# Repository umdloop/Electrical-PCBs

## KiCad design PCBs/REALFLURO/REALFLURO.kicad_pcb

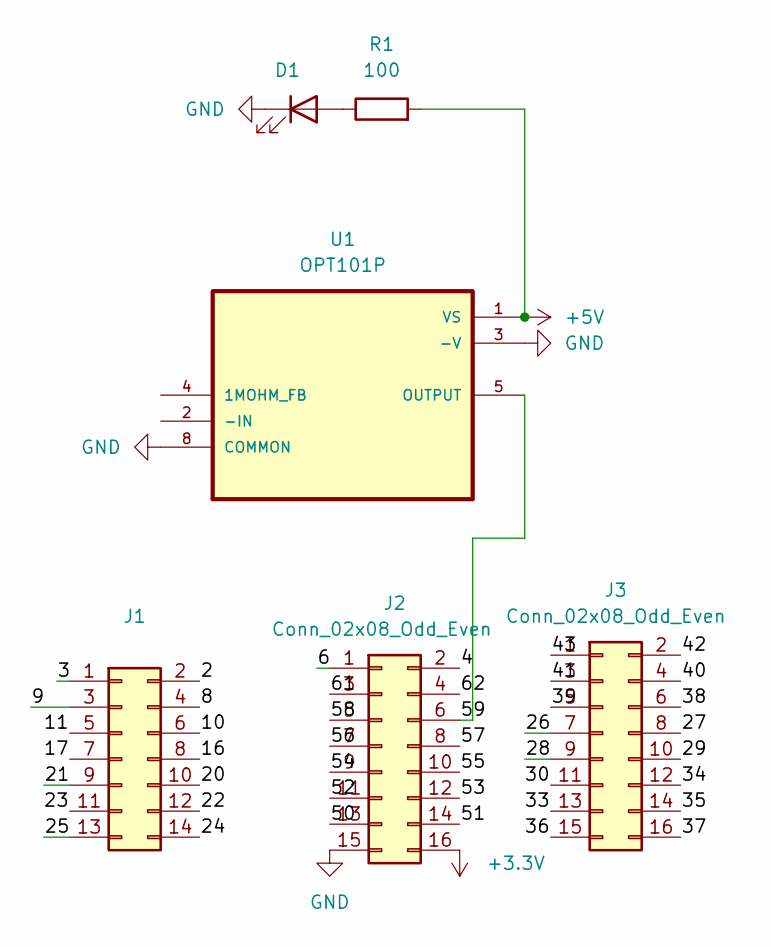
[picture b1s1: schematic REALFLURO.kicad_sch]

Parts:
D1: LED; LED_D3.0mm_Horizontal_O1.27mm_Z2.0mm_Clear
J1: Conn_02x07_Odd_Even; PinHeader_2x07_P2.54mm_Vertical
J2, J3: Conn_02x08_Odd_Even; PinHeader_2x08_P2.54mm_Vertical
R1: 100; R_0201_0603Metric
U1: OPT101P; DIP762W46P254L952H419Q8

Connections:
+3.3V: J2.16
+5V: R1.2, U1.1 (VS)
/2: J1.2
/3: J1.1
/4: J2.2
/6: J2.1
/8: J1.4
/9: J1.3
/10: J1.6
/11: J1.5
/16: J1.8
/17: J1.7
/20: J1.10
/21: J1.9
/22: J1.12
/23: J1.11
/24: J1.14
/25: J1.13
/26: J3.7
/27: J3.8
/28: J3.9
/29: J3.10
/30: J3.11
/33: J3.13
/34: J3.12
/35: J3.14
/36: J3.15
/37: J3.16
/38: J3.6
/39: J3.5
/40: J3.4
/41: J3.3
/42: J3.2
/43: J3.1
/50: J2.13
/51: J2.14
/52: J2.11
/53: J2.12
/54: J2.9
/55: J2.10
/56: J2.7
/57: J2.8
/58: J2.5
/59: J2.6, U1.5 (OUTPUT)
/61: J2.3
/62: J2.4
GND: D1.1 (K), J2.15, U1.3 (-V), U1.8 (COMMON)
unnamed: D1.2 (A), R1.1

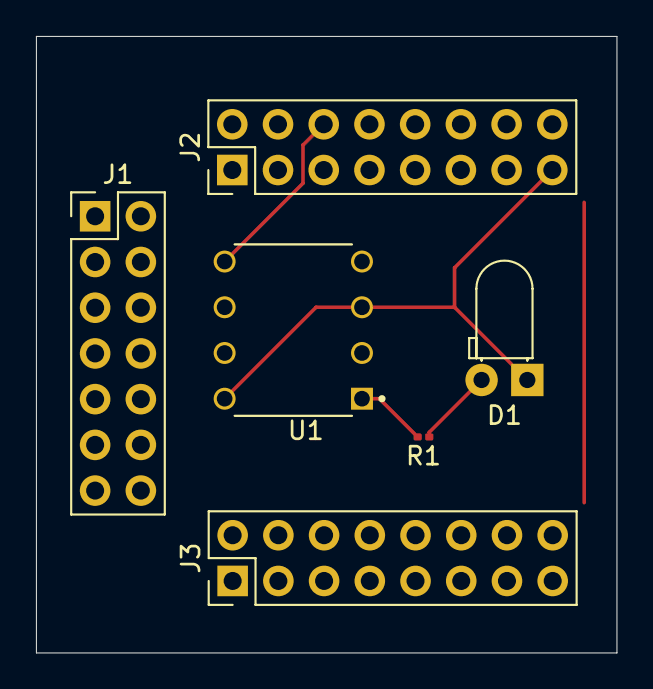
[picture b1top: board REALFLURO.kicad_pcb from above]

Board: 2 copper layers, 32.2 x 34.2 mm, 6 parts (0 on the bottom side), 4 nets.

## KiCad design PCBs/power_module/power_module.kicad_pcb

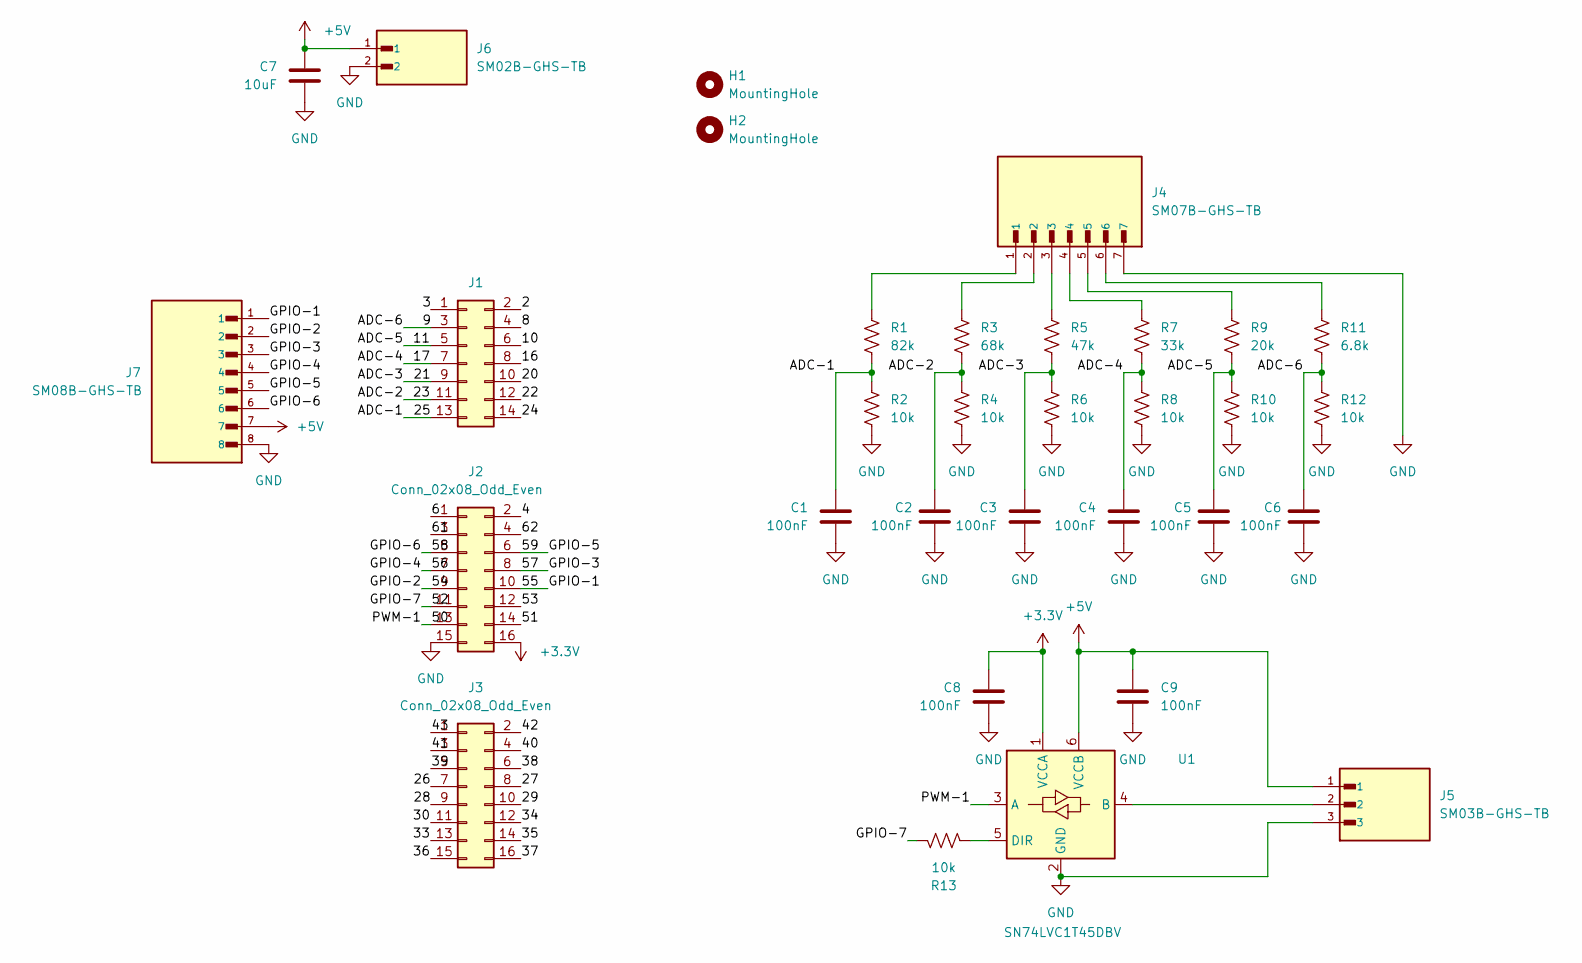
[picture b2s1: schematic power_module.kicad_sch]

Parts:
C1, C2, C3, C4, C5, C6, C8, C9: 100nF; C_0805_2012Metric_Pad1.18x1.45mm_HandSolder
C7: 10uF; C_0805_2012Metric_Pad1.18x1.45mm_HandSolder
H1, H2: MountingHole; MountingHole_3.2mm_M3
J1: Conn_02x07_Odd_Even; PinHeader_2x07_P2.54mm_Vertical
J2, J3: Conn_02x08_Odd_Even; PinHeader_2x08_P2.54mm_Vertical
J4: SM07B-GHS-TB; JST_GH_SM07B-GHS-TB_1x07-1MP_P1.25mm_Horizontal
J5: SM03B-GHS-TB; JST_GH_SM03B-GHS-TB_1x03-1MP_P1.25mm_Horizontal
J6: SM02B-GHS-TB; JST_SM02B-GHS-TB
J7: SM08B-GHS-TB; JST_GH_SM08B-GHS-TB_1x08-1MP_P1.25mm_Horizontal
R1: 82k; R_0805_2012Metric_Pad1.20x1.40mm_HandSolder
R2, R4, R6, R8, R10, R12, R13: 10k; R_0805_2012Metric_Pad1.20x1.40mm_HandSolder
R3: 68k; R_0805_2012Metric_Pad1.20x1.40mm_HandSolder
R5: 47k; R_0805_2012Metric_Pad1.20x1.40mm_HandSolder
R7: 33k; R_0805_2012Metric_Pad1.20x1.40mm_HandSolder
R9: 20k; R_0805_2012Metric_Pad1.20x1.40mm_HandSolder
R11: 6.8k; R_0805_2012Metric_Pad1.20x1.40mm_HandSolder
U1: SN74LVC1T45DBV; SOT-23-6

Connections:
+3.3V: C8.1, J2.16, U1.1 (VCCA)
+5V: C7.1, C9.1, J5.1, J6.1, J7.7, U1.6 (VCCB)
/2: J1.2
/3: J1.1
/4: J2.2
/6: J2.1
/8: J1.4
/9: C6.1, J1.3, R11.2, R12.1
/10: J1.6
/11: C5.1, J1.5, R9.2, R10.1
/16: J1.8
/17: C4.1, J1.7, R7.2, R8.1
/20: J1.10
/21: C3.1, J1.9, R5.2, R6.1
/22: J1.12
/23: C2.1, J1.11, R3.2, R4.1
/24: J1.14
/25: C1.1, J1.13, R1.2, R2.1
/27: J3.8
/29: J3.10
/30: J3.11
/33: J3.13
/34: J3.12
/35: J3.14
/36: J3.15
/37: J3.16
/38: J3.6
/39: J3.5
/40: J3.4
/41: J3.3
/42: J3.2
/43: J3.1
/50: J2.13, U1.3 (A)
/51: J2.14
/52: J2.11, R13.1
/53: J2.12
/54: J2.9, J7.2
/55: J2.10, J7.1
/56: J2.7, J7.4
/57: J2.8, J7.3
/58: J2.5, J7.6
/59: J2.6, J7.5
/61: J2.3
/62: J2.4
GND: C1.2, C2.2, C3.2, C4.2, C5.2, C6.2, C7.2, C8.2, C9.2, J2.15, J4.7, J5.3, J6.2, J7.8, R2.2, R4.2, R6.2, R8.2, R10.2, R12.2, U1.2 (GND)
unnamed: J4.1, R1.1
unnamed: J4.2, R3.1
unnamed: J4.3, R5.1
unnamed: J4.4, R7.1
unnamed: J4.5, R9.1
unnamed: J4.6, R11.1
unnamed: J5.2, U1.4 (B)
unnamed: R13.2, U1.5 (DIR)

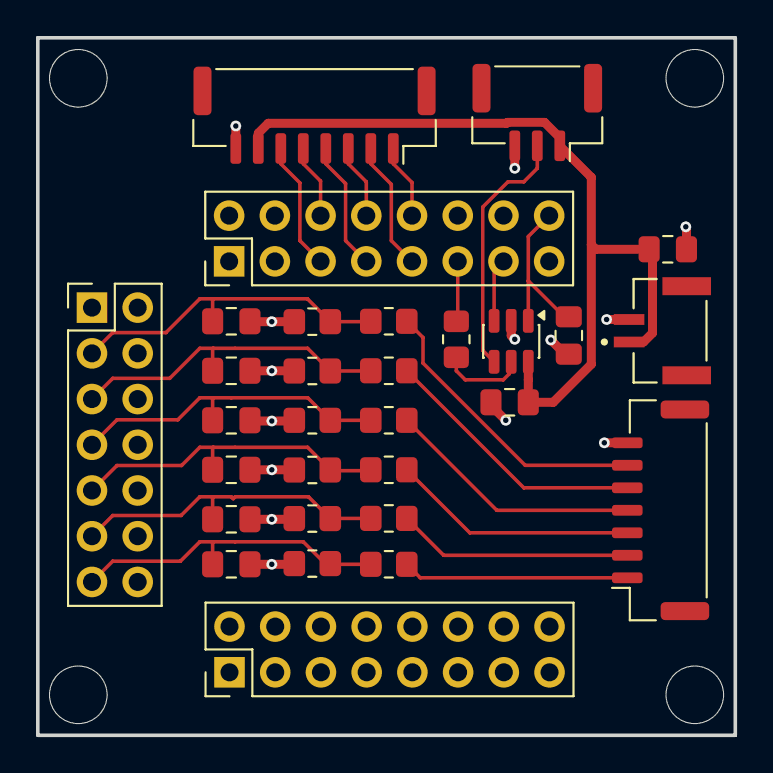
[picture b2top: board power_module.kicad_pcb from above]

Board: 2 copper layers, 38.8 x 38.8 mm, 34 parts (0 on the bottom side), 25 nets.

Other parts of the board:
H3, H4: MountingHole; MountingHole_3.2mm_M3

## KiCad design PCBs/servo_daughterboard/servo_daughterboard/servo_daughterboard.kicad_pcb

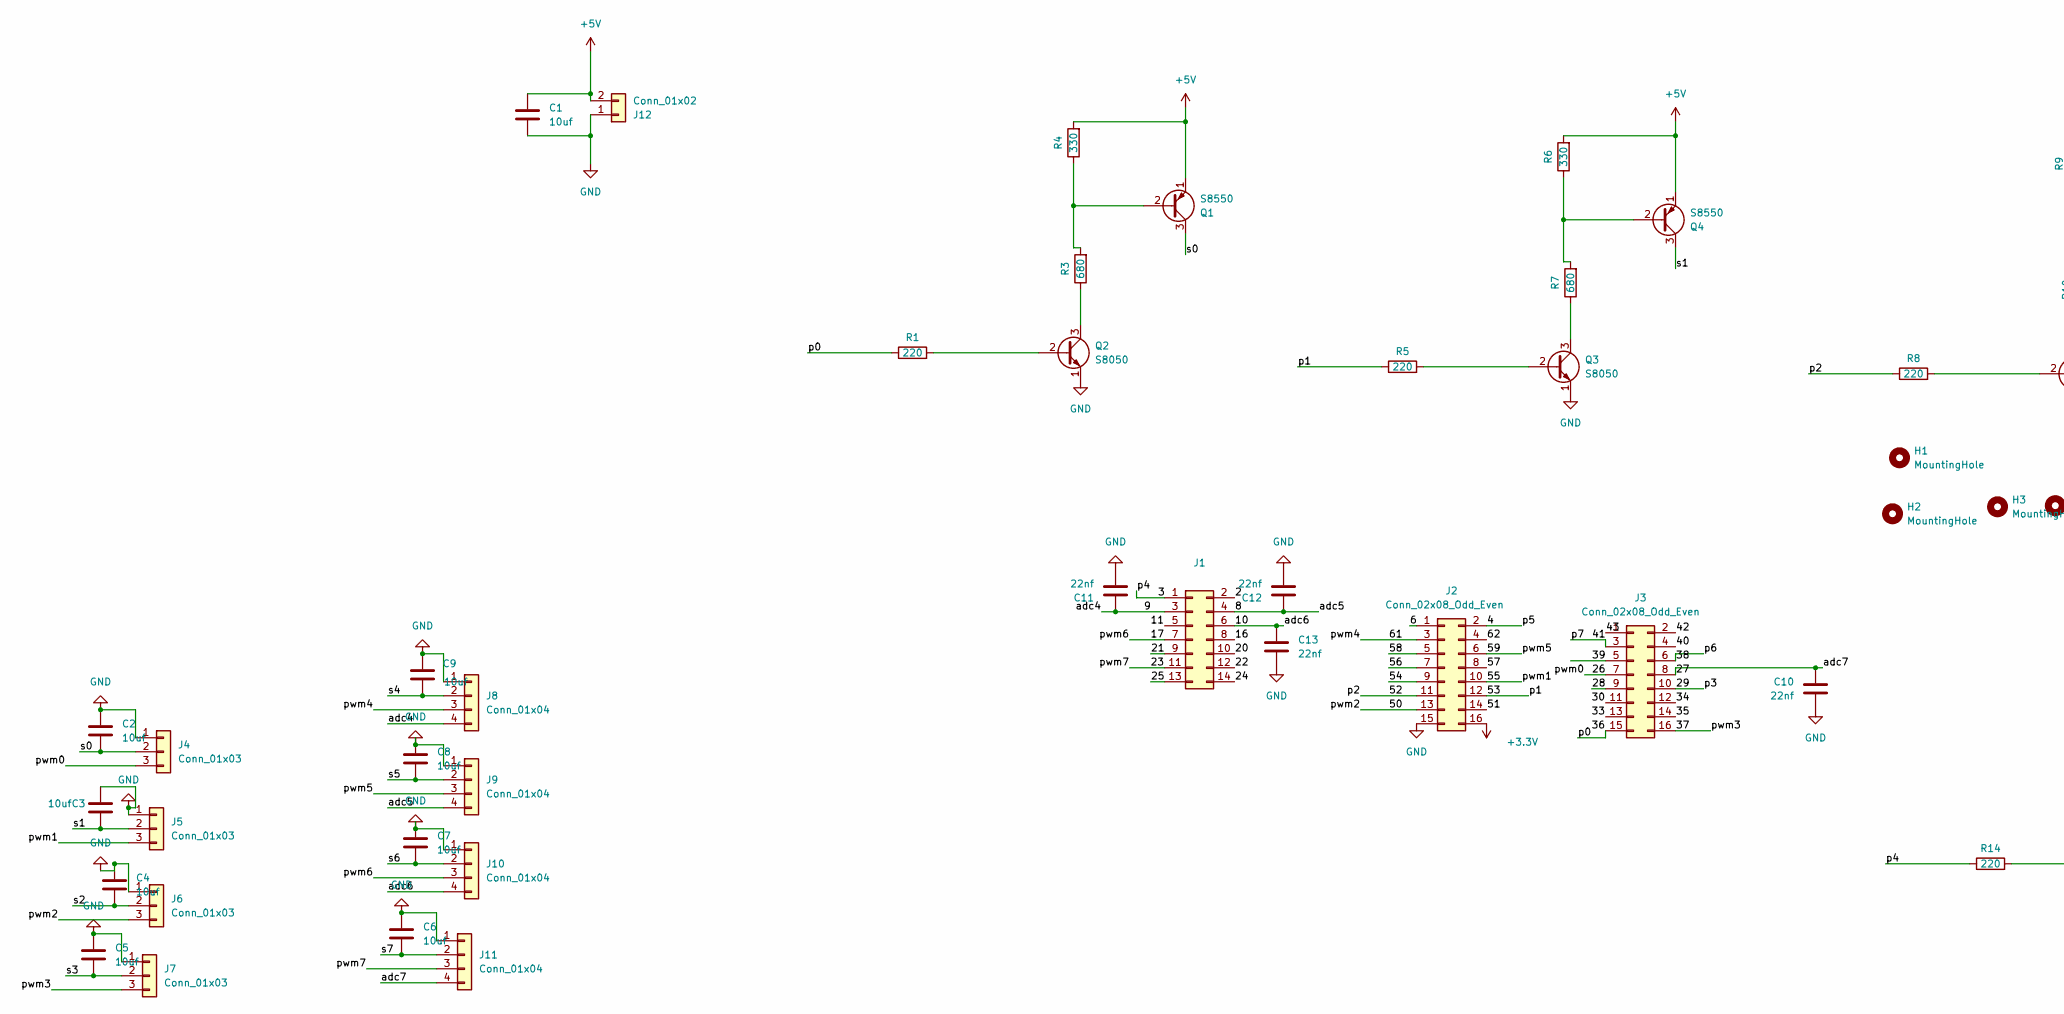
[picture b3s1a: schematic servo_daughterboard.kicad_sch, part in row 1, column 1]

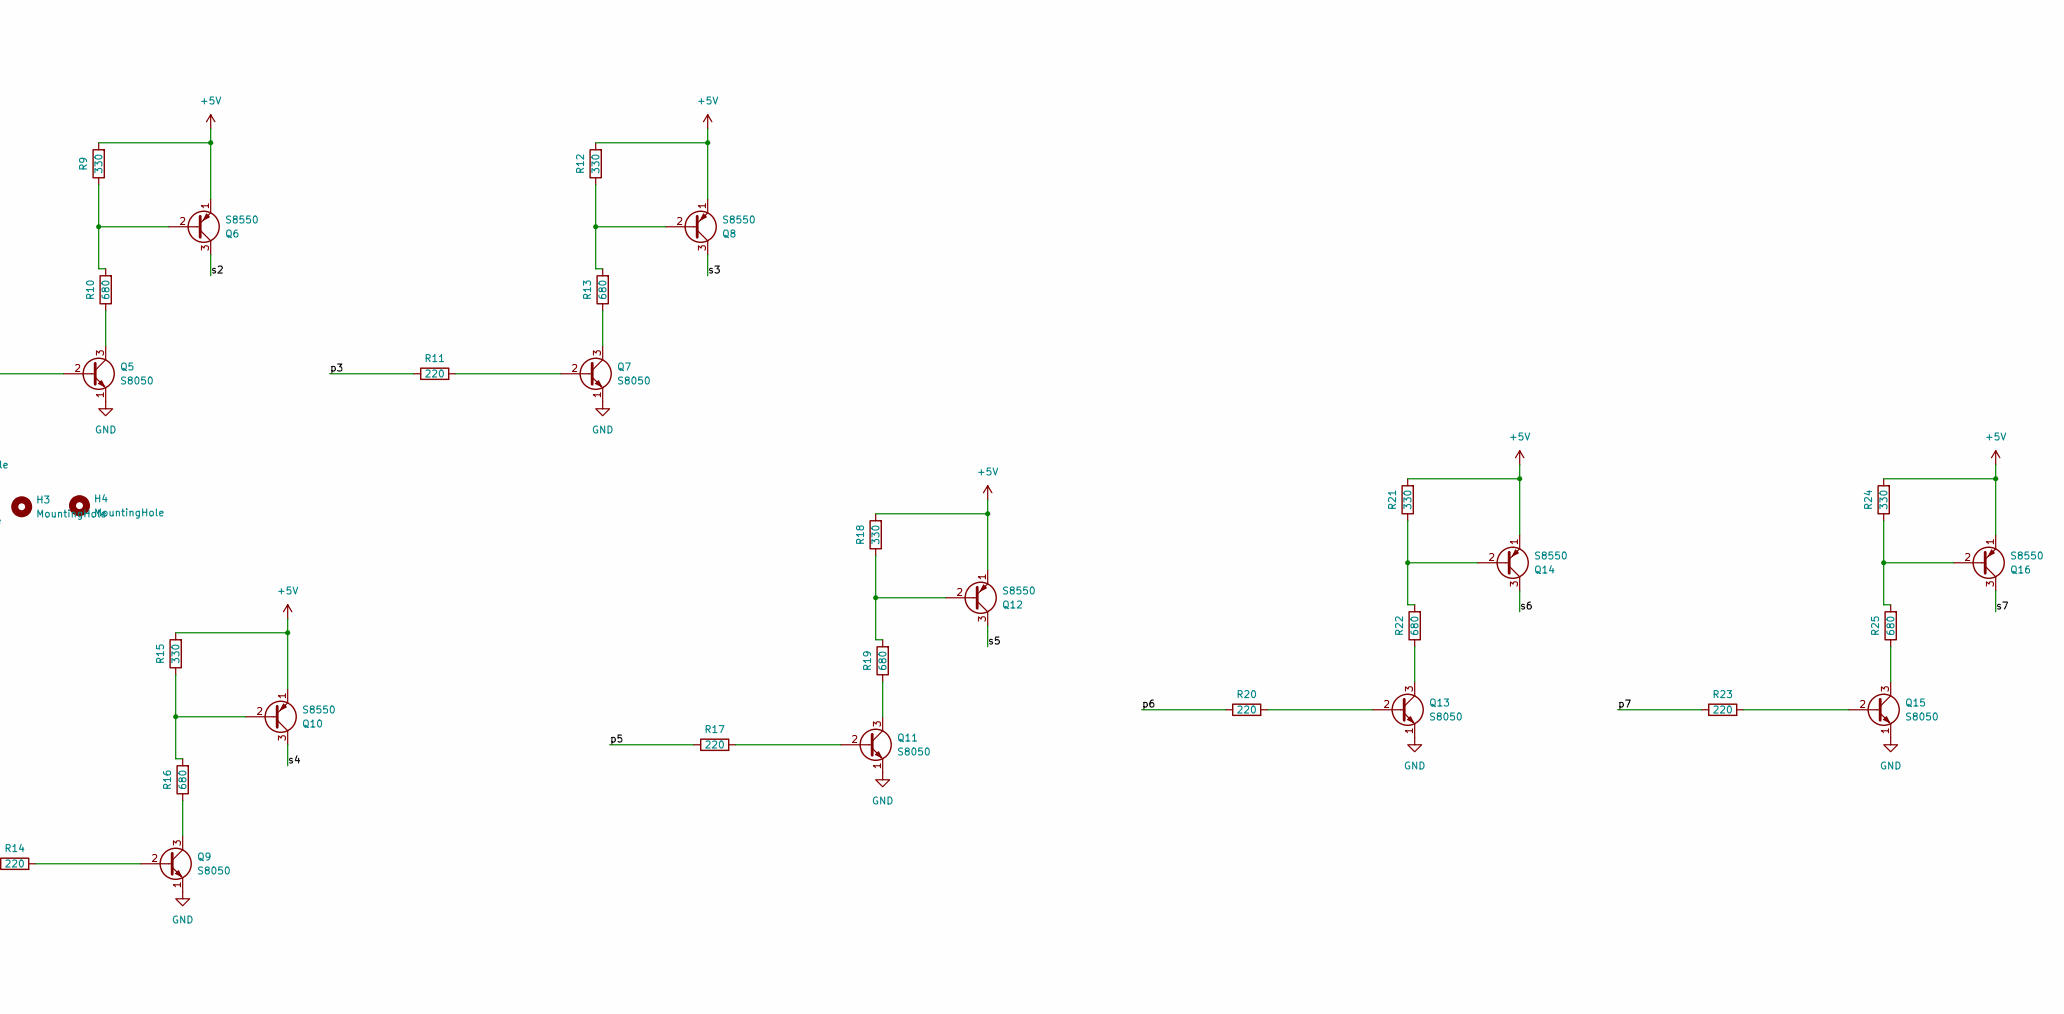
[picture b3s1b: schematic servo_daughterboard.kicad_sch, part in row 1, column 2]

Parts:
C1, C2, C3, C4, C5, C6, C7, C8, C9: 10uf; C_0805_2012Metric_Pad1.18x1.45mm_HandSolder
C10, C11, C12, C13: 22nf; C_0805_2012Metric_Pad1.18x1.45mm_HandSolder
H1, H2, H3, H4: MountingHole; MountingHole_2.2mm_M2
J1: Conn_02x07_Odd_Even; PinHeader_2x07_P2.54mm_Vertical
J2, J3: Conn_02x08_Odd_Even; PinHeader_2x08_P2.54mm_Vertical
J4, J5, J6, J7: Conn_01x03; JST_XH_S3B-XH-A_1x03_P2.50mm_Horizontal
J8, J9, J10, J11: Conn_01x04; JST_XH_S4B-XH-A_1x04_P2.50mm_Horizontal
J12: Conn_01x02; JST_XH_S2B-XH-A_1x02_P2.50mm_Horizontal
Q1, Q4, Q6, Q8, Q10, Q12, Q14, Q16: S8550; TO-92_Inline
Q2, Q3, Q5, Q7, Q9, Q11, Q13, Q15: S8050; TO-92_Inline
R1, R5, R8, R11, R14, R17, R20, R23: 220; R_0402_1005Metric_Pad0.72x0.64mm_HandSolder
R3, R7, R10, R13, R16, R19, R22, R25: 680; R_0402_1005Metric_Pad0.72x0.64mm_HandSolder
R4, R6, R9, R12, R15, R18, R21, R24: 330; R_0402_1005Metric_Pad0.72x0.64mm_HandSolder

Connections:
+3.3V: J2.16
+5V: C1.1, J12.2, Q1.1 (E), Q4.1 (E), Q6.1 (E), Q8.1 (E), Q10.1 (E), Q12.1 (E), Q14.1 (E), Q16.1 (E), R4.2, R6.2, R9.2, R12.2, R15.2, R18.2, R21.2, R24.2
/2: J1.2
/3: J1.1, R14.1
/4: J2.2, R17.1
/6: J2.1
/8: C12.1, J1.4, J9.4
/9: C11.1, J1.3, J8.4
/10: C13.1, J1.6, J10.4
/11: J1.5
/16: J1.8
/17: J1.7, J10.3
/20: J1.10
/21: J1.9
/22: J1.12
/23: J1.11, J11.3
/24: J1.14
/25: J1.13
/26: J3.7, J4.3
/27: C10.1, J3.8, J11.4
/28: J3.9
/29: J3.10, R11.1
/30: J3.11
/33: J3.13
/34: J3.12
/35: J3.14
/36: J3.15, R1.1
/37: J3.16, J7.3
/38: J3.6, R20.1
/39: J3.5
/40: J3.4
/41: J3.3, R23.1
/42: J3.2
/43: J3.1
/50: J2.13, J6.3
/51: J2.14
/52: J2.11, R8.1
/53: J2.12, R5.1
/54: J2.9
/55: J2.10, J5.3
/56: J2.7
/57: J2.8
/58: J2.5
/59: J2.6, J9.3
/61: J2.3, J8.3
/62: J2.4
/s0: C2.2, J4.2, Q1.3 (C)
/s1: C3.2, J5.2, Q4.3 (C)
/s2: C4.2, J6.2, Q6.3 (C)
/s3: C5.2, J7.2, Q8.3 (C)
/s4: C9.2, J8.2, Q10.3 (C)
/s5: C8.2, J9.2, Q12.3 (C)
/s6: C7.2, J10.2, Q14.3 (C)
/s7: C6.2, J11.2, Q16.3 (C)
GND: C1.2, C2.1, C3.1, C4.1, C5.1, C6.1, C7.1, C8.1, C9.1, C10.2, C11.2, C12.2, C13.2, J2.15, J4.1, J5.1, J6.1, J7.1, J8.1, J9.1, J10.1, J11.1, J12.1, Q2.1 (E), Q3.1 (E), Q5.1 (E), Q7.1 (E), Q9.1 (E), Q11.1 (E), Q13.1 (E), Q15.1 (E)
unnamed: Q1.2 (B), R3.2, R4.1
unnamed: Q2.2 (B), R1.2
unnamed: Q2.3 (C), R3.1
unnamed: Q3.2 (B), R5.2
unnamed: Q3.3 (C), R7.1
unnamed: Q4.2 (B), R6.1, R7.2
unnamed: Q5.2 (B), R8.2
unnamed: Q5.3 (C), R10.1
unnamed: Q6.2 (B), R9.1, R10.2
unnamed: Q7.2 (B), R11.2
unnamed: Q7.3 (C), R13.1
unnamed: Q8.2 (B), R12.1, R13.2
unnamed: Q9.2 (B), R14.2
unnamed: Q9.3 (C), R16.1
unnamed: Q10.2 (B), R15.1, R16.2
unnamed: Q11.2 (B), R17.2
unnamed: Q11.3 (C), R19.1
unnamed: Q12.2 (B), R18.1, R19.2
unnamed: Q13.2 (B), R20.2
unnamed: Q13.3 (C), R22.1
unnamed: Q14.2 (B), R21.1, R22.2
unnamed: Q15.2 (B), R23.2
unnamed: Q15.3 (C), R25.1
unnamed: Q16.2 (B), R24.1, R25.2

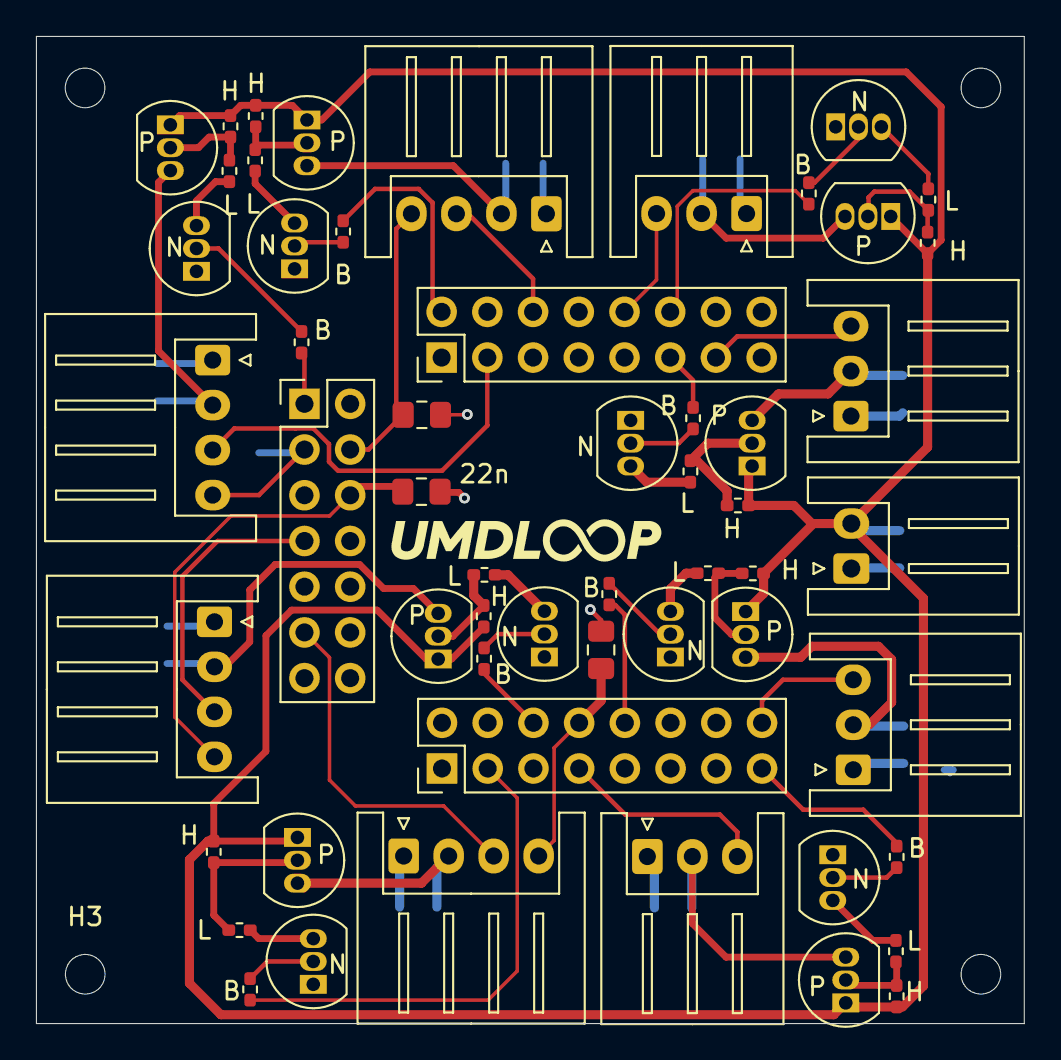
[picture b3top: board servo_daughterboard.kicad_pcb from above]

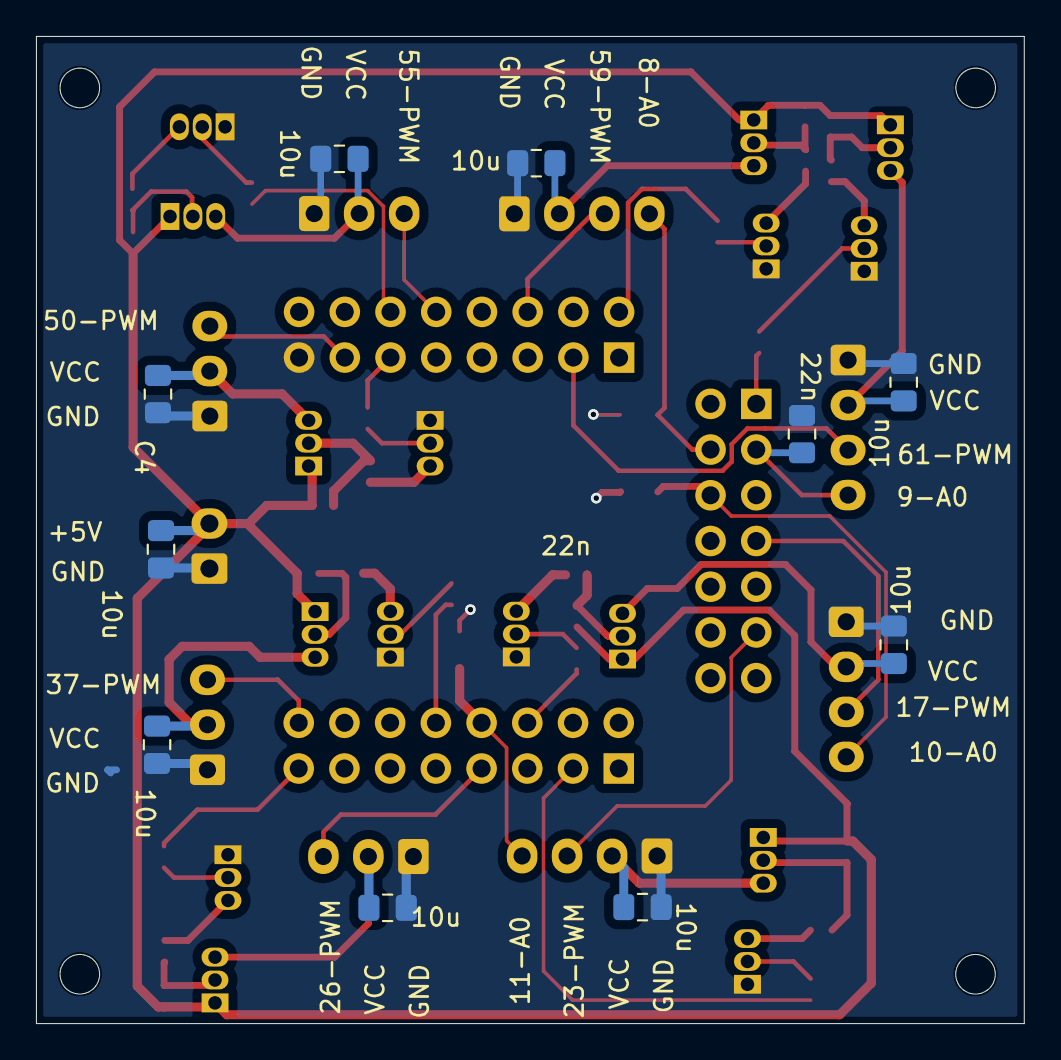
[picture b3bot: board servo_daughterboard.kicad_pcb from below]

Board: 2 copper layers, 54.9 x 54.8 mm, 69 parts (10 on the bottom side), 54 nets.

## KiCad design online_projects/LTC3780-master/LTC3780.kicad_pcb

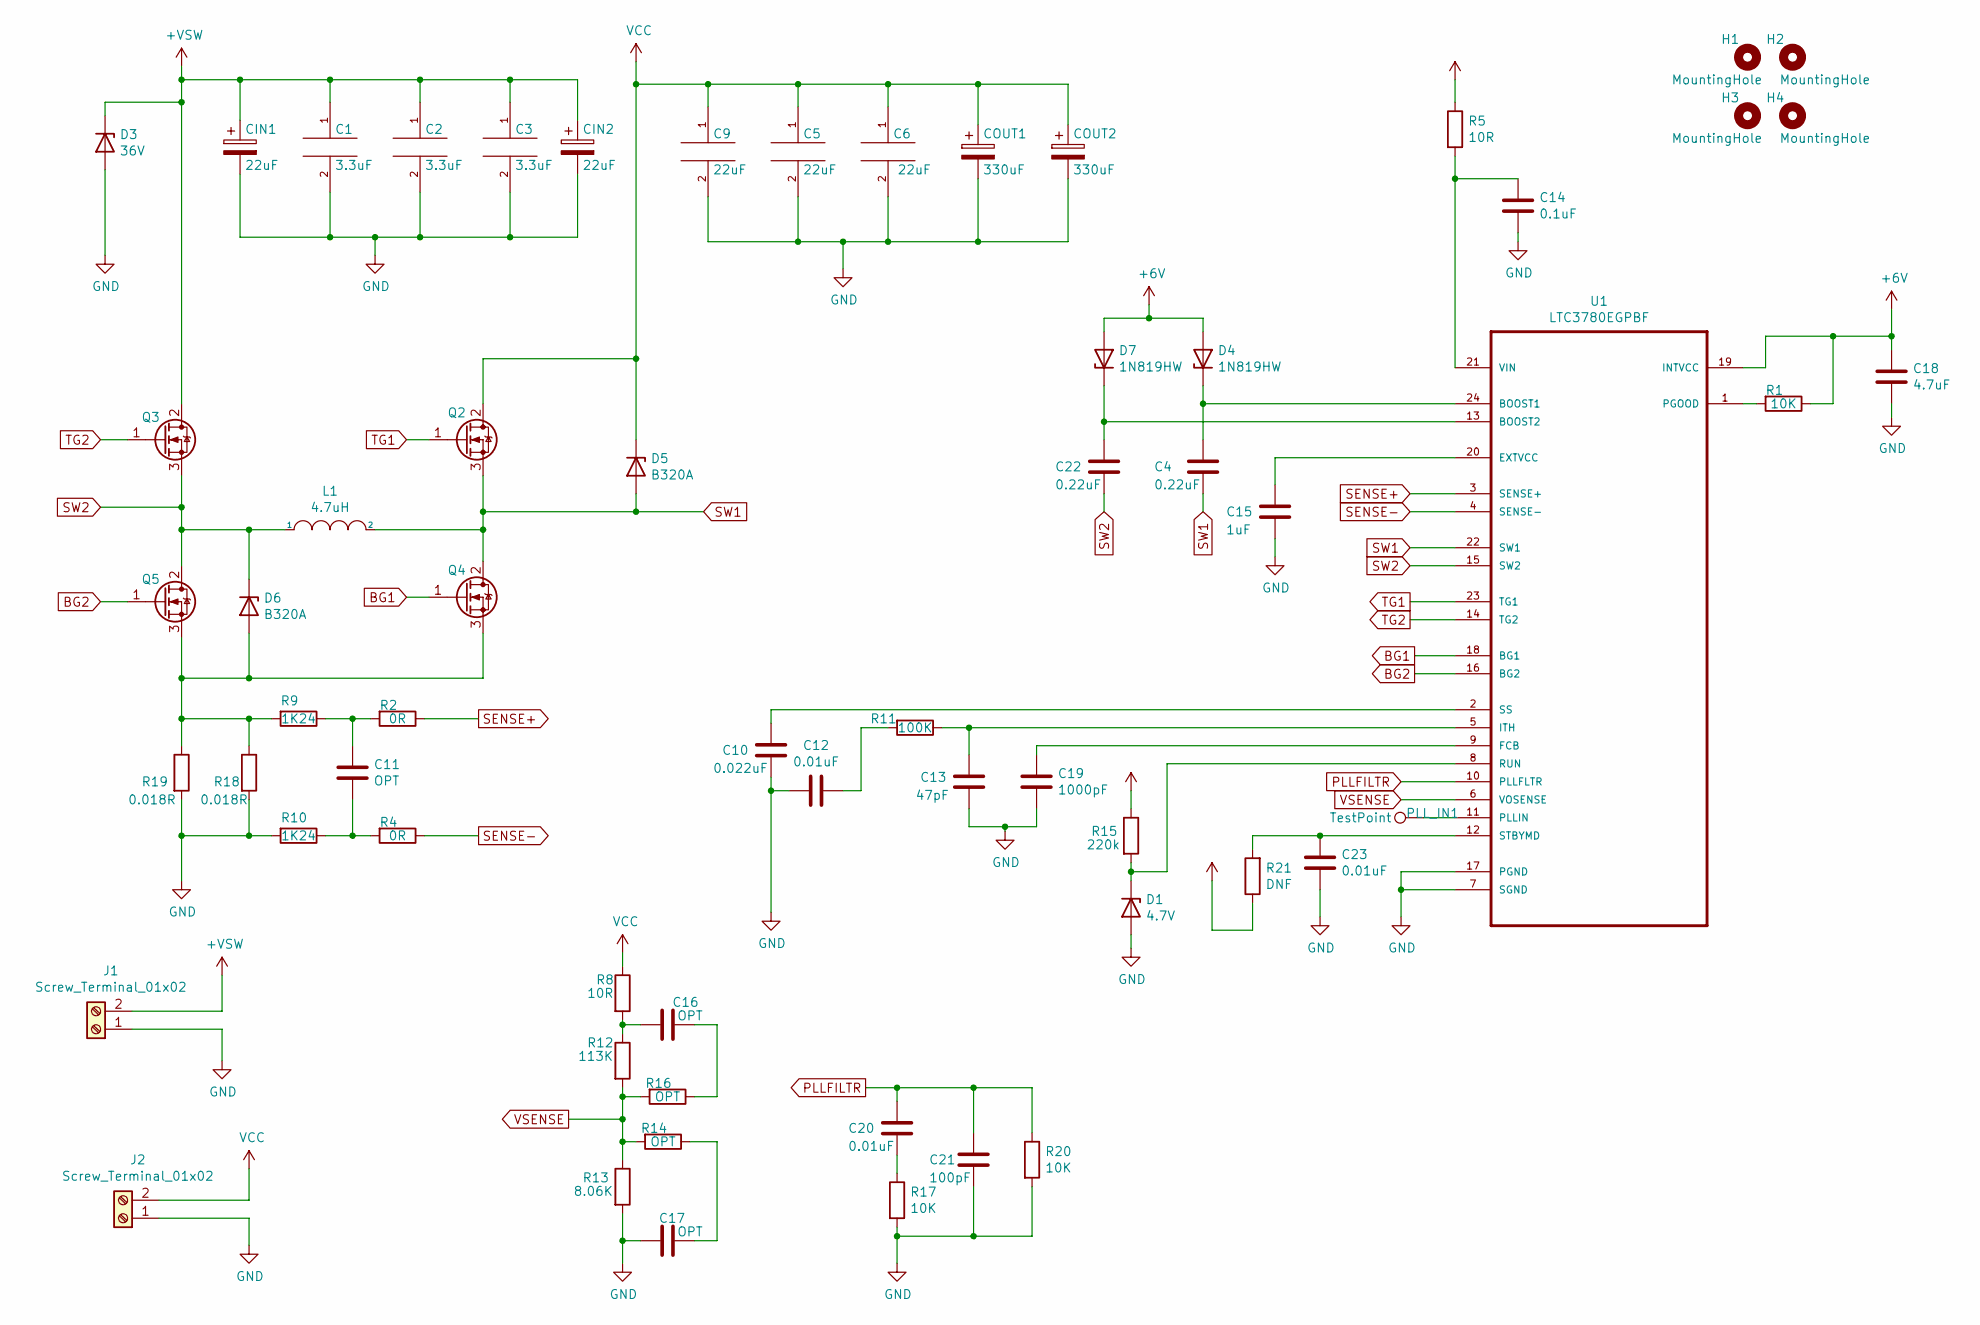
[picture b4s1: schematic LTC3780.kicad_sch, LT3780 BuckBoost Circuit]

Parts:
C1, C2, C3: 3.3uF; C_0603_HandSoldering
C4, C22: 0.22uF; C_0603_HandSoldering
C5, C6, C9: 22uF; C_0603_HandSoldering
C10: 0.022uF; C_0603_HandSoldering
C11, C16, C17: OPT; C_0603_HandSoldering
C12, C20, C23: 0.01uF; C_0603_HandSoldering
C13: 47pF; C_0603_HandSoldering
C14: 0.1uF; C_0603_HandSoldering
C15: 1uF; C_0603_HandSoldering
C18: 4.7uF; C_0603_HandSoldering
C19: 1000pF; C_0603_HandSoldering
C21: 100pF; C_0603_HandSoldering
CIN1, CIN2: 22uF; CP_Elec_8x6.7
COUT1, COUT2: 330uF; CP_Elec_8x10.5
D1: 4.7V; D_SOD-323_HandSoldering
D3: 36V; D_SOT-23_ANK
D4, D7: 1N819HW; D_SOD-123
D5, D6: B320A; D_SMA_Handsoldering
H1, H2, H3, H4: MountingHole; MountingHole_4mm
J1, J2: Screw_Terminal_01x02; JST_VH_B2P-VH_2x3.96mm_Vertical
L1: 4.7uH; Inductor_Wurth_MAPI-4020
PLL_IN1: TestPoint; Measurement_Point_Square-SMD-Pad_Small
Q2, Q3, Q4, Q5: IPD100N04S402ATMA1; TO-252-2
R1, R17, R20: 10K; R_0603_HandSoldering
R2, R4: 0R; R_0603_HandSoldering
R5, R8: 10R; R_0603_HandSoldering
R9, R10: 1K24; R_0603_HandSoldering
R11: 100K; R_0603_HandSoldering
R12: 113K; R_0603_HandSoldering
R13: 8.06K; R_0603_HandSoldering
R14, R16: OPT; R_0603_HandSoldering
R15: 220k; R_0603_HandSoldering
R18, R19: 0.018R; R_2512_HandSoldering
R21: DNF; R_0603_HandSoldering
U1: LTC3780EGPBF; SOP65P780X200-24N

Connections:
+6V: C18.1, D4.2 (A), D7.2 (A), R1.1, U1.19 (INTVCC)
+VSW: C1.1, C2.1, C3.1, CIN1.1, CIN2.1, D3.1 (K), J1.2, Q3.2, R5.1, R15.1, R21.1
BG1: Q4.1, U1.18 (BG1)
BG2: Q5.1, U1.16 (BG2)
GND: C1.2, C2.2, C3.2, C5.2, C6.2, C9.2, C10.2, C12.2, C13.2, C14.2, C15.1, C17.2, C18.2, C19.2, C21.2, C23.2, CIN1.2, CIN2.2, COUT1.2, COUT2.2, D1.2 (A), D3.2 (A), J1.1, J2.1, R10.2, R13.2, R17.2, R18.2, R19.2, R20.2, U1.7 (SGND), U1.17 (PGND)
unnamed: C4.1, D4.1 (K), U1.24 (BOOST1)
unnamed: C10.1, U1.2 (SS)
unnamed: C11.1, R2.2, R9.1
unnamed: C11.2, R4.2, R10.1
unnamed: C12.1, R11.2
unnamed: C13.1, R11.1, U1.5 (ITH)
unnamed: C14.1, R5.2, U1.21 (VIN)
unnamed: C15.2, U1.20 (EXTVCC)
unnamed: C16.1, R16.1
unnamed: C16.2, R8.2, R12.1
unnamed: C17.1, R14.1
unnamed: C19.1, U1.9 (FCB)
unnamed: C20.2, R17.1
unnamed: C22.1, D7.1 (K), U1.13 (BOOST2)
unnamed: C23.1, R21.2, U1.12 (STBYMD)
unnamed: D1.1 (K), R15.2, U1.8 (RUN)
unnamed: D6.2 (A), Q4.3, Q5.3, R9.2, R18.1, R19.1
unnamed: PLL_IN1.1, U1.11 (PLLIN)
unnamed: R1.2, U1.1 (PGOOD)
PLLFILTR: C20.1, C21.1, R20.1, U1.10 (PLLFLTR)
SENSE+: R2.1, U1.3 (SENSE+)
SENSE-: R4.1, U1.4 (SENSE-)
SW1: C4.2, D5.2 (A), L1.2, Q2.3, Q4.2, U1.22 (SW1)
SW2: C22.2, D6.1 (K), L1.1, Q3.3, Q5.2, U1.15 (SW2)
TG1: Q2.1, U1.23 (TG1)
TG2: Q3.1, U1.14 (TG2)
VCC: C5.1, C6.1, C9.1, COUT1.1, COUT2.1, D5.1 (K), J2.2, Q2.2, R8.1
VSENSE: R12.2, R13.1, R14.2, R16.2, U1.6 (VOSENSE)

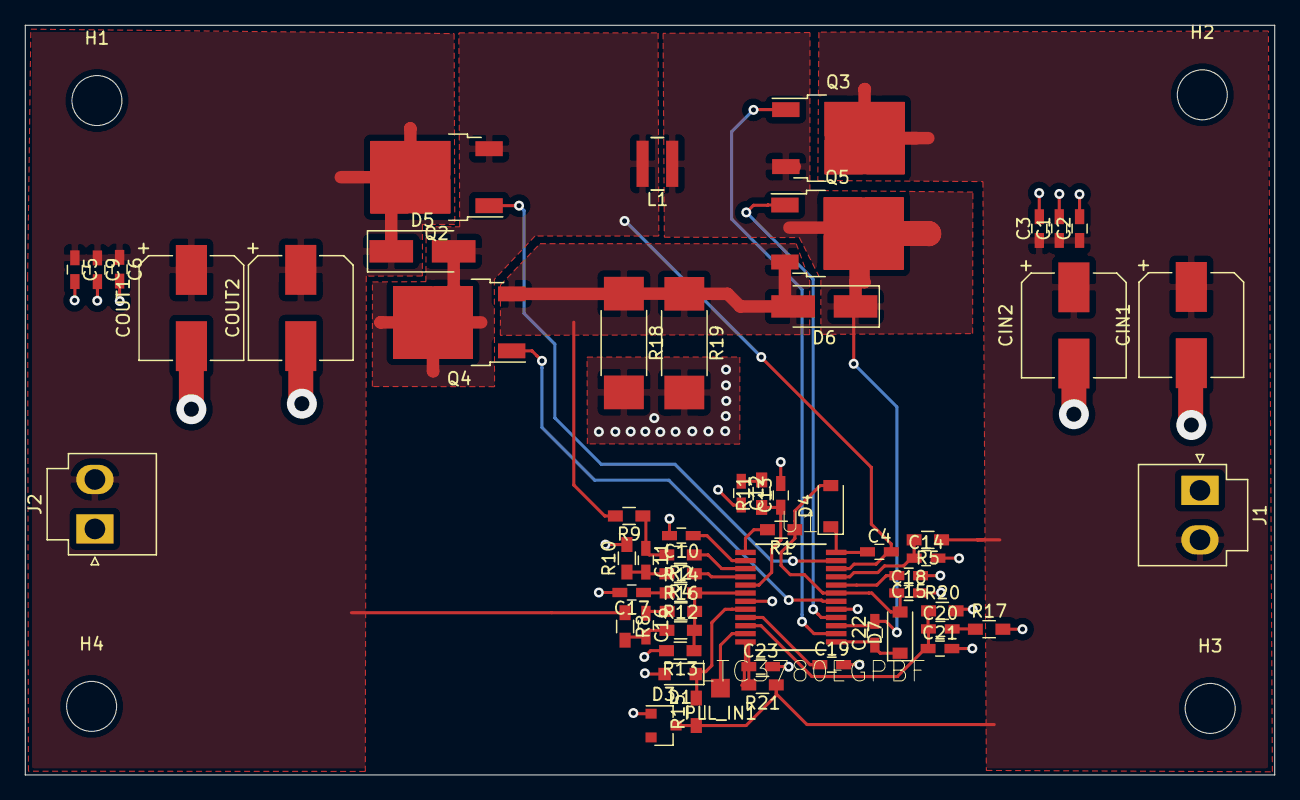
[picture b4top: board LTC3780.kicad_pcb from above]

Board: 2 copper layers, 100.0 x 60.0 mm, 62 parts (0 on the bottom side), 33 nets.

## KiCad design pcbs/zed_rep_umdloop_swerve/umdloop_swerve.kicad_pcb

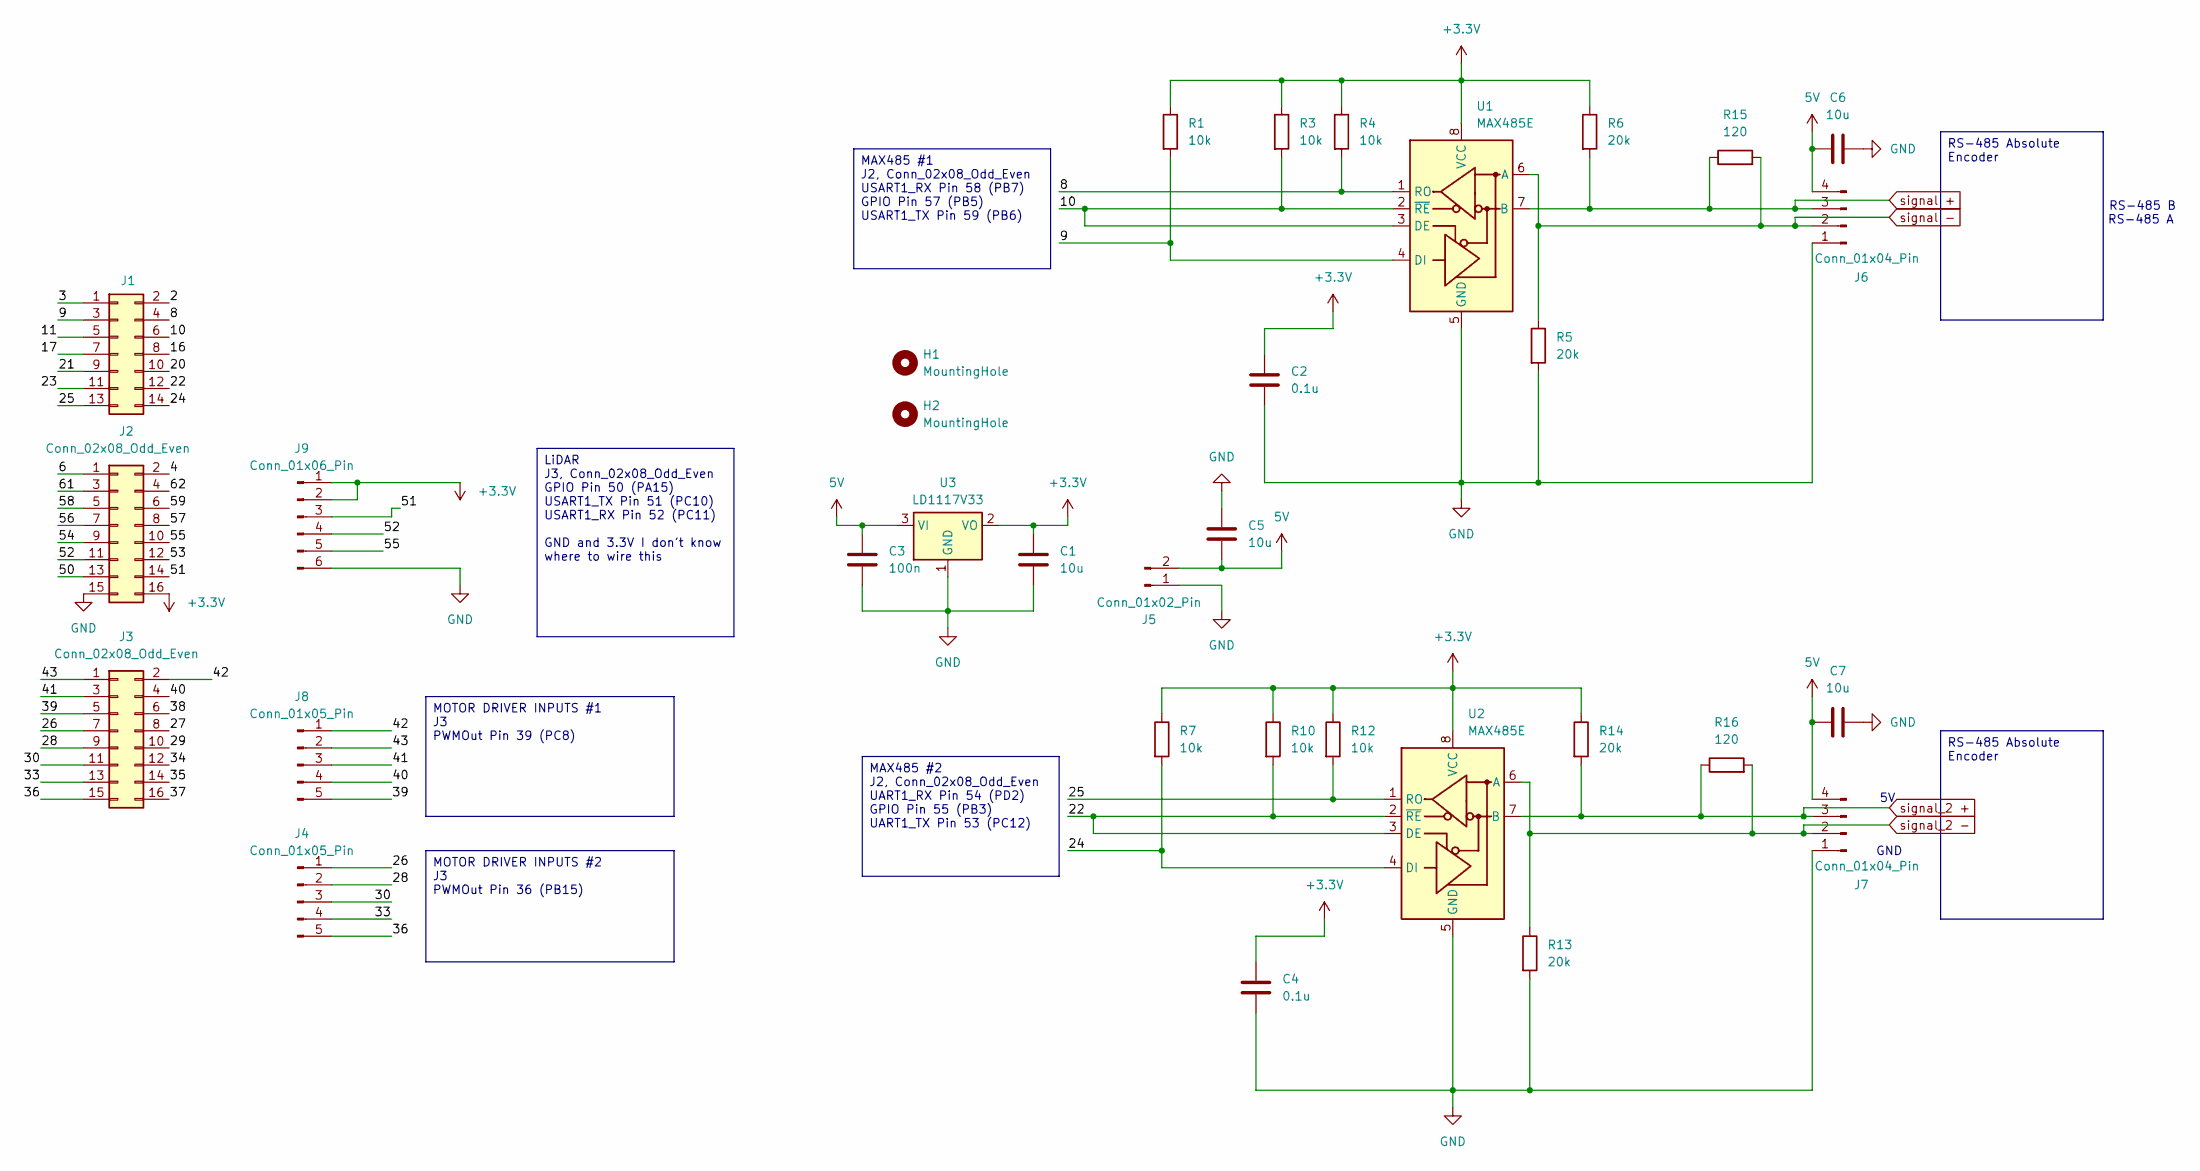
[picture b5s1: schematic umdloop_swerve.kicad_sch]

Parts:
C1, C5, C6, C7: 10u; C_0805_2012Metric_Pad1.18x1.45mm_HandSolder
C2, C4: 0.1u; C_0402_1005Metric_Pad0.74x0.62mm_HandSolder
C3: 100n; C_0805_2012Metric_Pad1.18x1.45mm_HandSolder
H1, H2: MountingHole; MountingHole_3.2mm_M3
J1: Conn_02x07_Odd_Even; PinHeader_2x07_P2.54mm_Vertical
J2, J3: Conn_02x08_Odd_Even; PinHeader_2x08_P2.54mm_Vertical
J4, J8: Conn_01x05_Pin; JST_XH_S5B-XH-A_1x05_P2.50mm_Horizontal
J5: Conn_01x02_Pin; JST_XH_S2B-XH-A_1x02_P2.50mm_Horizontal
J6, J7: Conn_01x04_Pin; JST_XH_S4B-XH-A_1x04_P2.50mm_Horizontal
J9: Conn_01x06_Pin; JST_XH_S6B-XH-A_1x06_P2.50mm_Horizontal
R1, R3, R4, R7, R10, R12: 10k; R_0402_1005Metric_Pad0.72x0.64mm_HandSolder
R5, R6, R13, R14: 20k; R_0402_1005Metric_Pad0.72x0.64mm_HandSolder
R15, R16: 120; R_0402_1005Metric_Pad0.72x0.64mm_HandSolder
U1, U2: MAX485E; SOIC-8_3.9x4.9mm_P1.27mm
U3: LD1117V33; SOT-223-3_TabPin2

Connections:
5V: C3.1, C5.1, C6.1, C7.1, J5.2, J6.4, J7.4, U3.3 (VI)
+3.3V: C1.1, C2.1, C4.1, J2.16, J9.1, J9.2, R1.1, R3.1, R4.1, R6.1, R7.1, R10.1, R12.1, R14.1, U1.8 (VCC), U2.8 (VCC), U3.2 (VO)
/2: J1.2
/3: J1.1
/4: J2.2
/6: J2.1
/8: J1.4, R4.2, U1.1 (RO)
/9: J1.3, R1.2, U1.4 (DI)
/10: J1.6, R3.2, U1.2 (~RE), U1.3 (DE)
/11: J1.5
/16: J1.8
/17: J1.7
/20: J1.10
/21: J1.9
/22: J1.12, R10.2, U2.2 (~RE), U2.3 (DE)
/23: J1.11
/24: J1.14, R7.2, U2.4 (DI)
/25: J1.13, R12.2, U2.1 (RO)
/26: J3.7, J4.1
/27: J3.8
/28: J3.9, J4.2
/29: J3.10
/30: J3.11, J4.3
/33: J3.13, J4.4
/34: J3.12
/35: J3.14
/36: J3.15, J4.5
/37: J3.16
/38: J3.6
/39: J3.5, J8.5
/40: J3.4, J8.4
/41: J3.3, J8.3
/42: J3.2, J8.1
/43: J3.1, J8.2
/50: J2.13
/51: J2.14, J9.3
/52: J2.11, J9.4
/53: J2.12
/54: J2.9
/55: J2.10, J9.5
/56: J2.7
/57: J2.8
/58: J2.5
/59: J2.6
/61: J2.3
/62: J2.4
GND: C1.2, C2.2, C3.2, C4.2, C5.2, C6.2, C7.2, J2.15, J5.1, J6.1, J7.1, J9.6, R5.2, R13.2, U1.5 (GND), U2.5 (GND), U3.1 (GND)
signal +: J6.3, R6.2, R15.1, U1.7 (B)
signal -: J6.2, R5.1, R15.2, U1.6 (A)
signal_2 +: J7.3, R14.2, R16.1, U2.7 (B)
signal_2 -: J7.2, R13.1, R16.2, U2.6 (A)

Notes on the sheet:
GND
RS-485 B
RS-485 A
RS-485 Absolute Encoder
MOTOR DRIVER INPUTS #2 J3 PWMOut Pin 36 (PB15)
MAX485 #1 J2, Conn_02x08_Odd_Even USART1_RX Pin 58 (PB7) GPIO Pin 57 (PB5) USART1_TX Pin 59 (PB6)
MAX485 #2 J2, Conn_02x08_Odd_Even UART1_RX Pin 54 (PD2) GPIO Pin 55 (PB3) UART1_TX Pin 53 (PC12)
LiDAR J3, Conn_02x08_Odd_Even GPIO Pin 50 (PA15) USART1_TX Pin 51 (PC10) USART1_RX Pin 52 (PC11) GND and 3.3V I don't know where to wire this
MOTOR DRIVER INPUTS #1 J3 PWMOut Pin 39 (PC8)
